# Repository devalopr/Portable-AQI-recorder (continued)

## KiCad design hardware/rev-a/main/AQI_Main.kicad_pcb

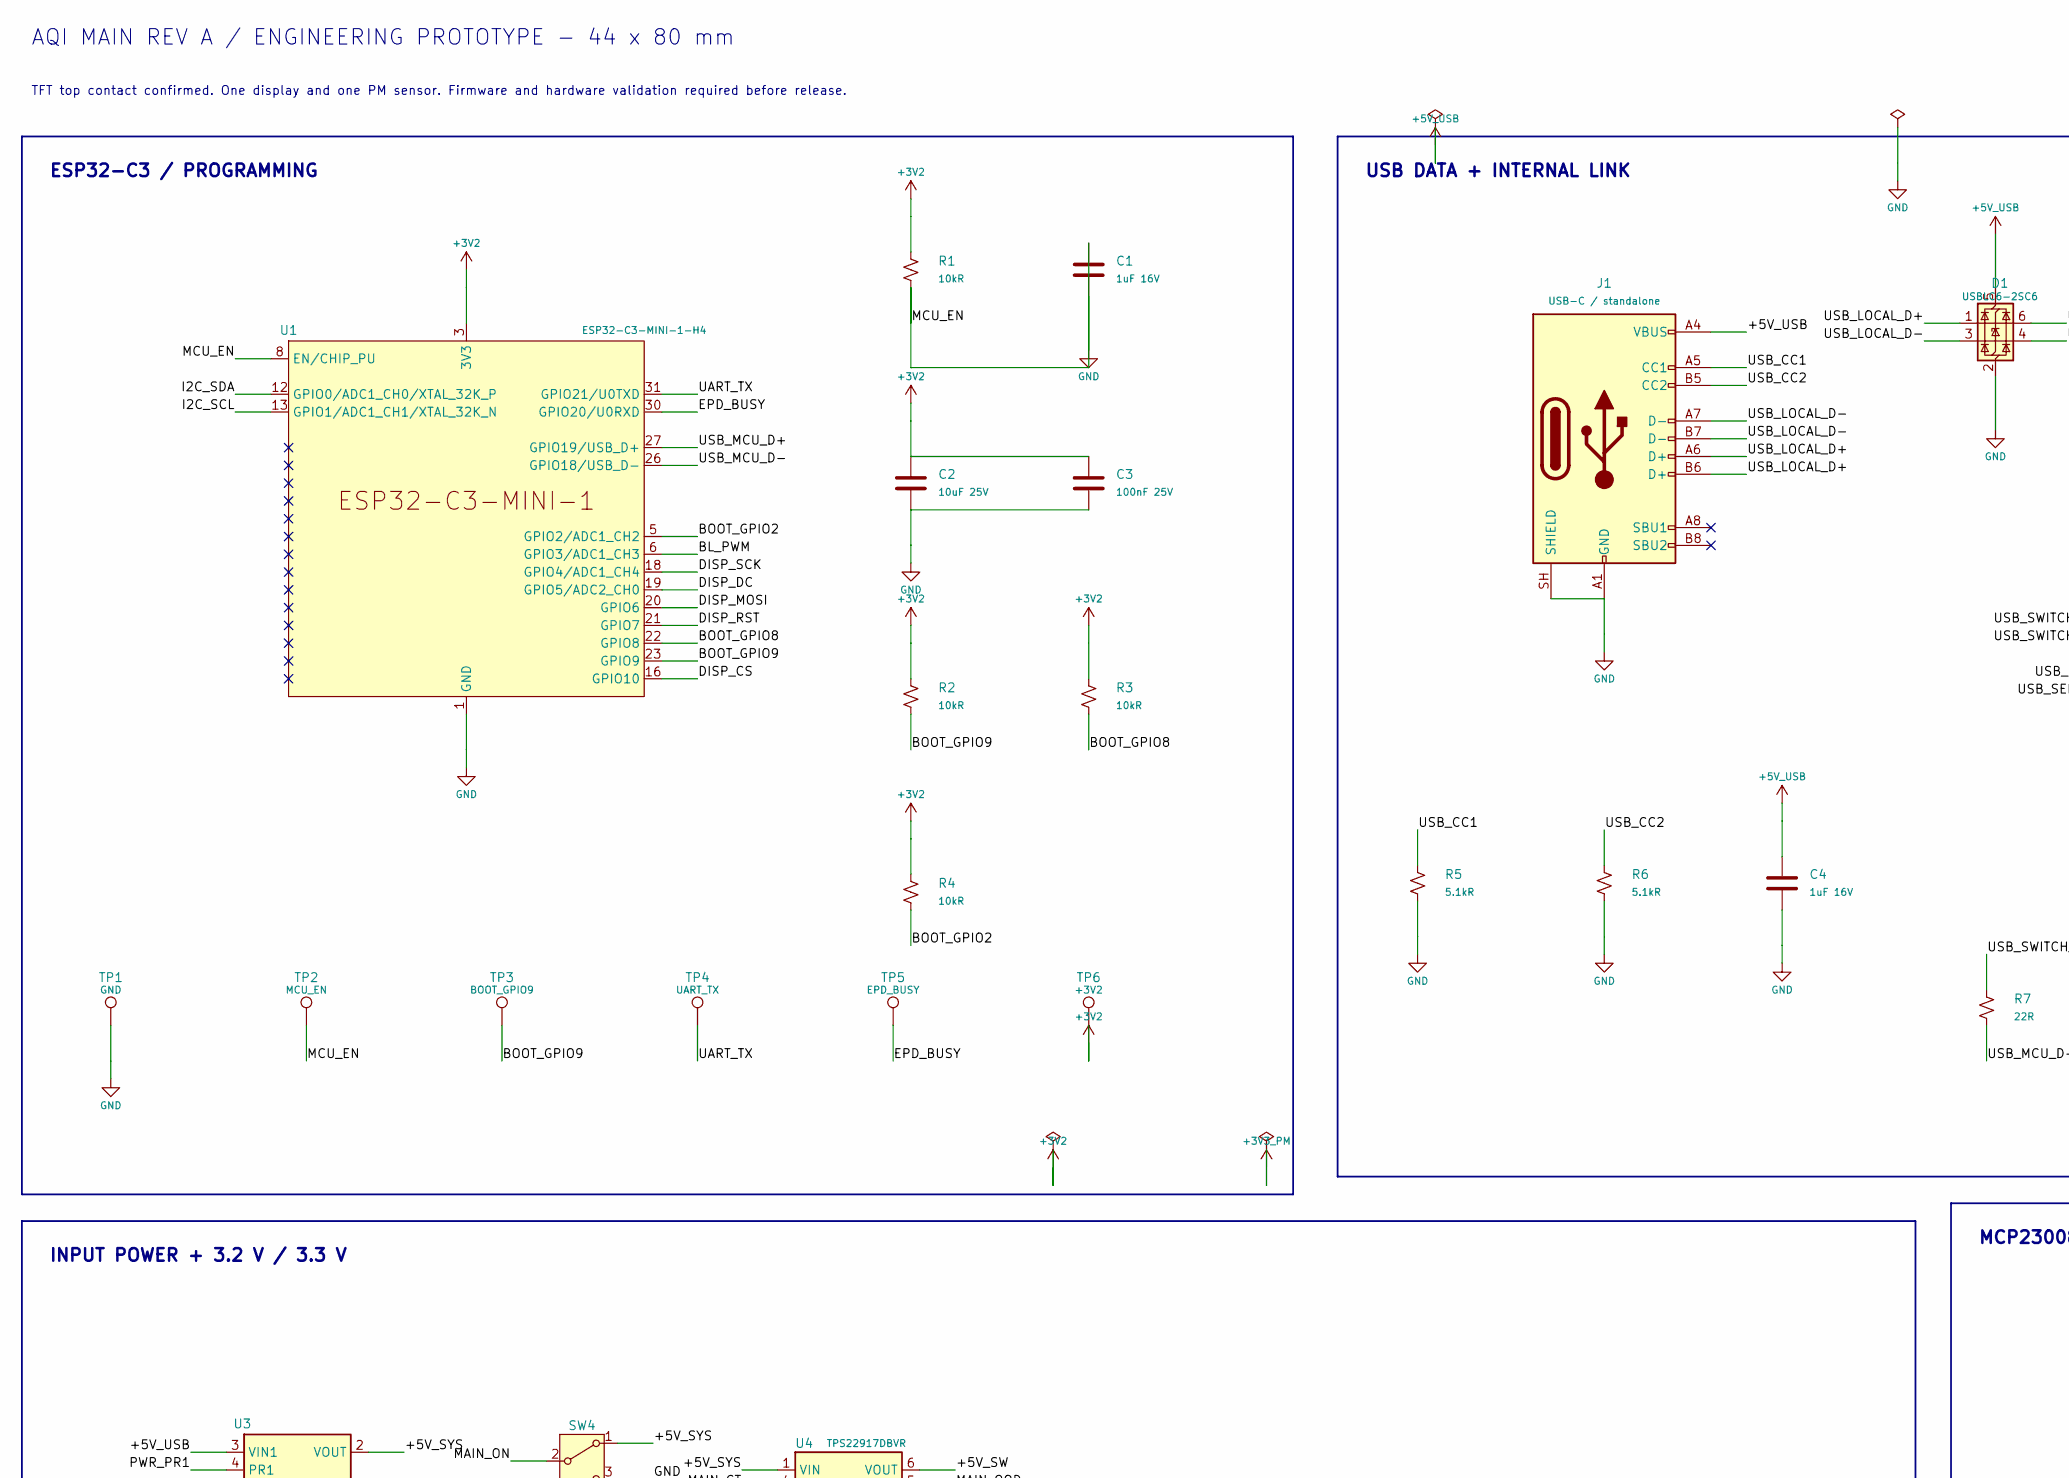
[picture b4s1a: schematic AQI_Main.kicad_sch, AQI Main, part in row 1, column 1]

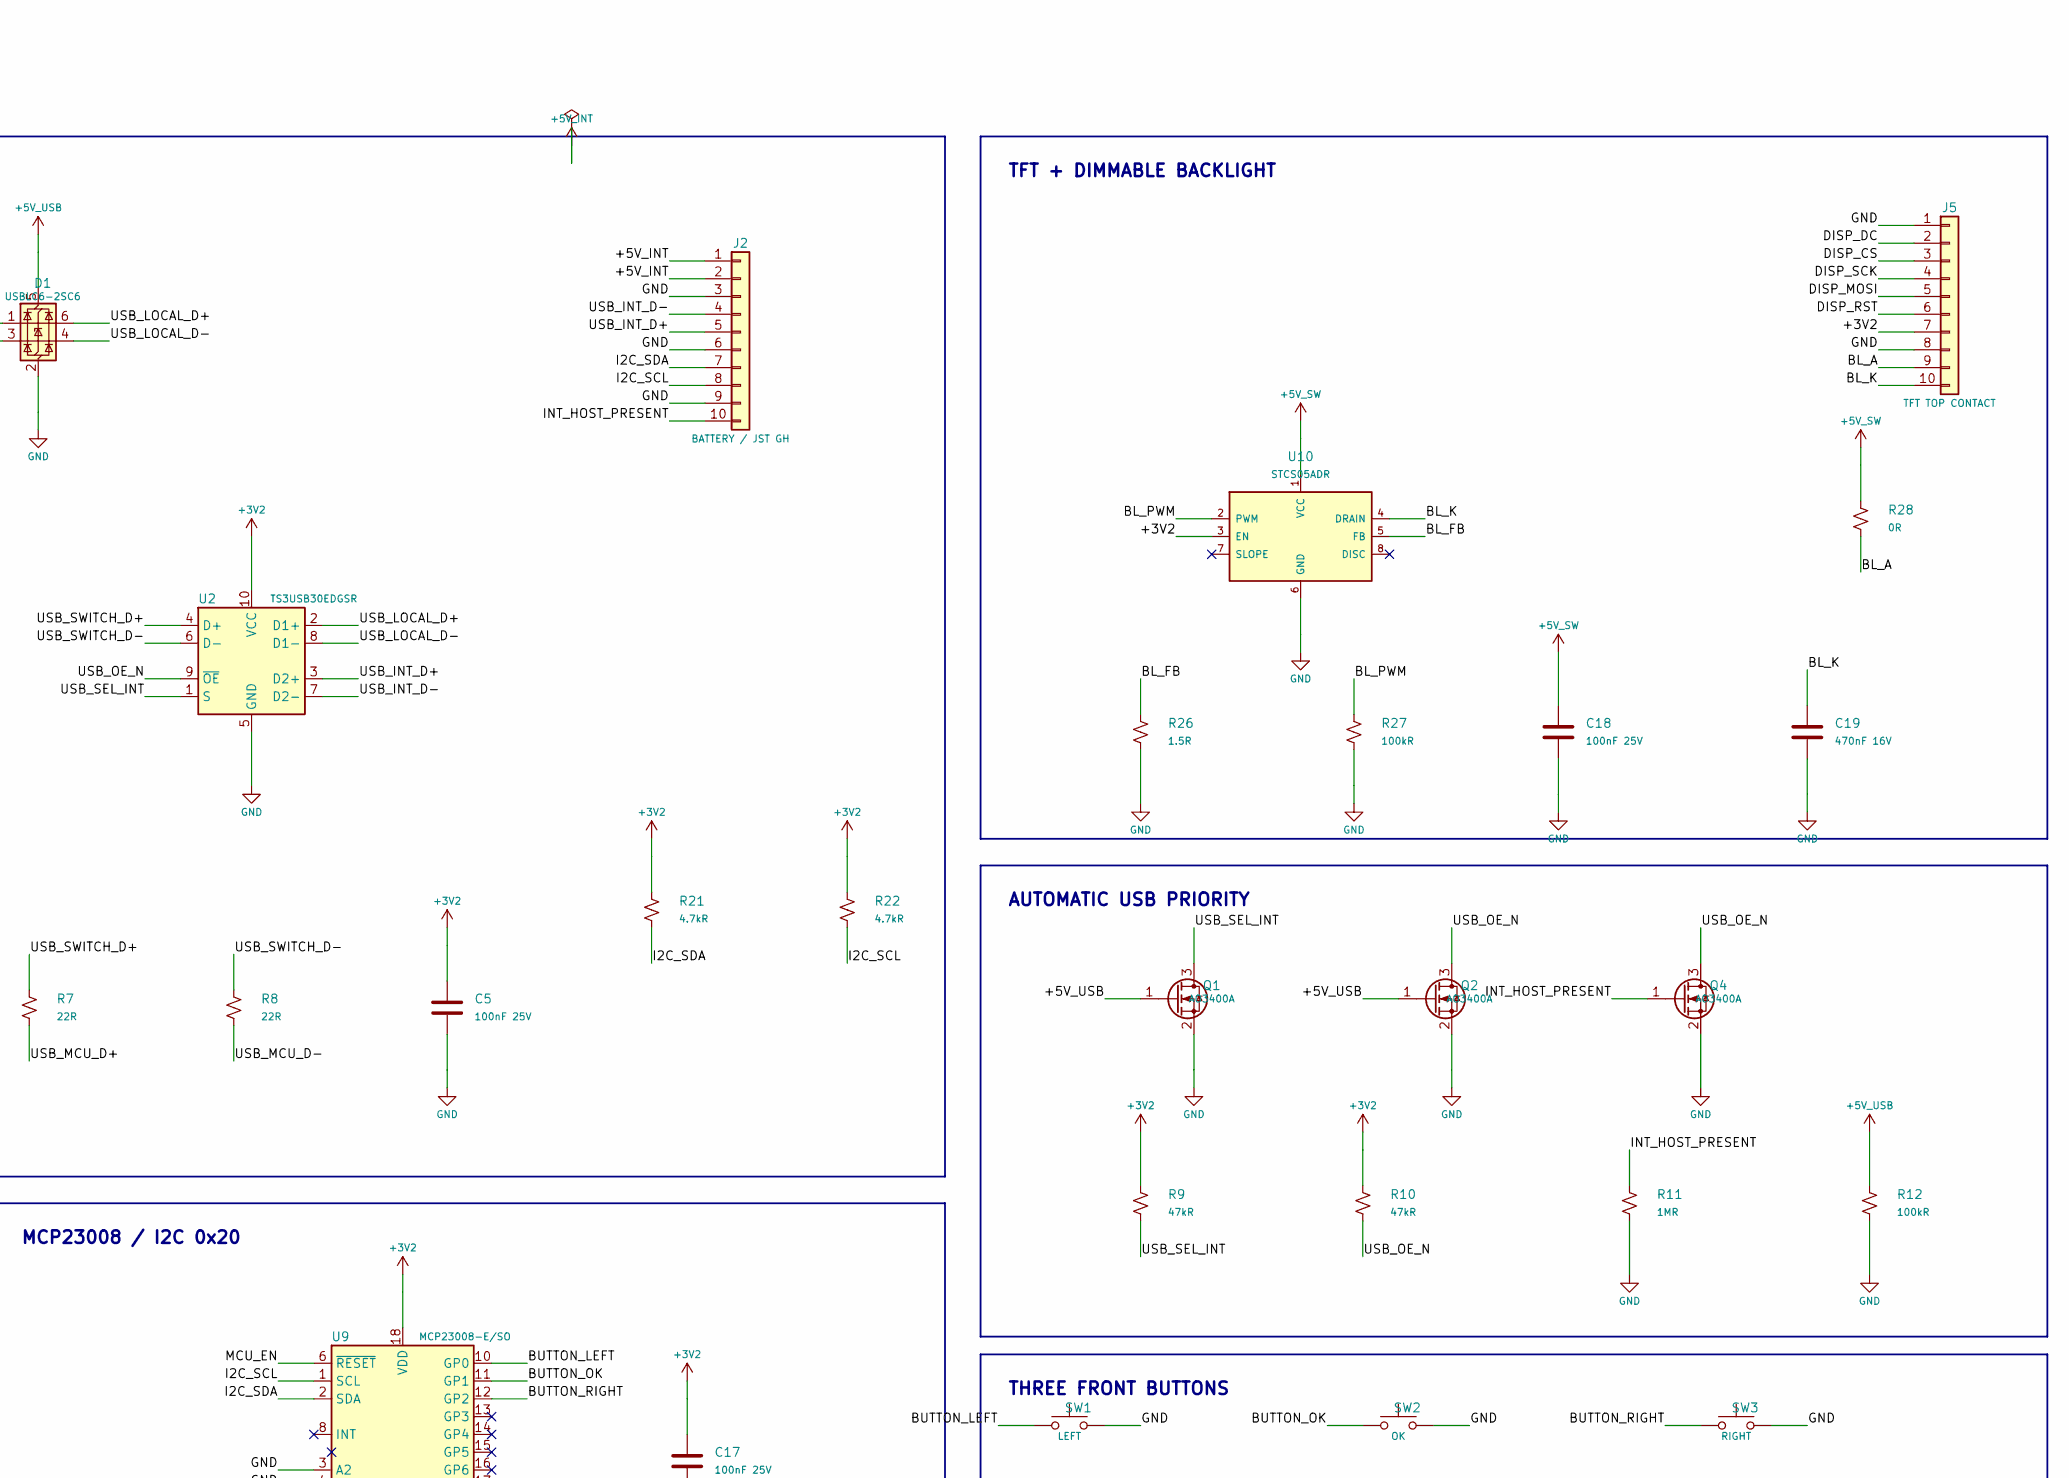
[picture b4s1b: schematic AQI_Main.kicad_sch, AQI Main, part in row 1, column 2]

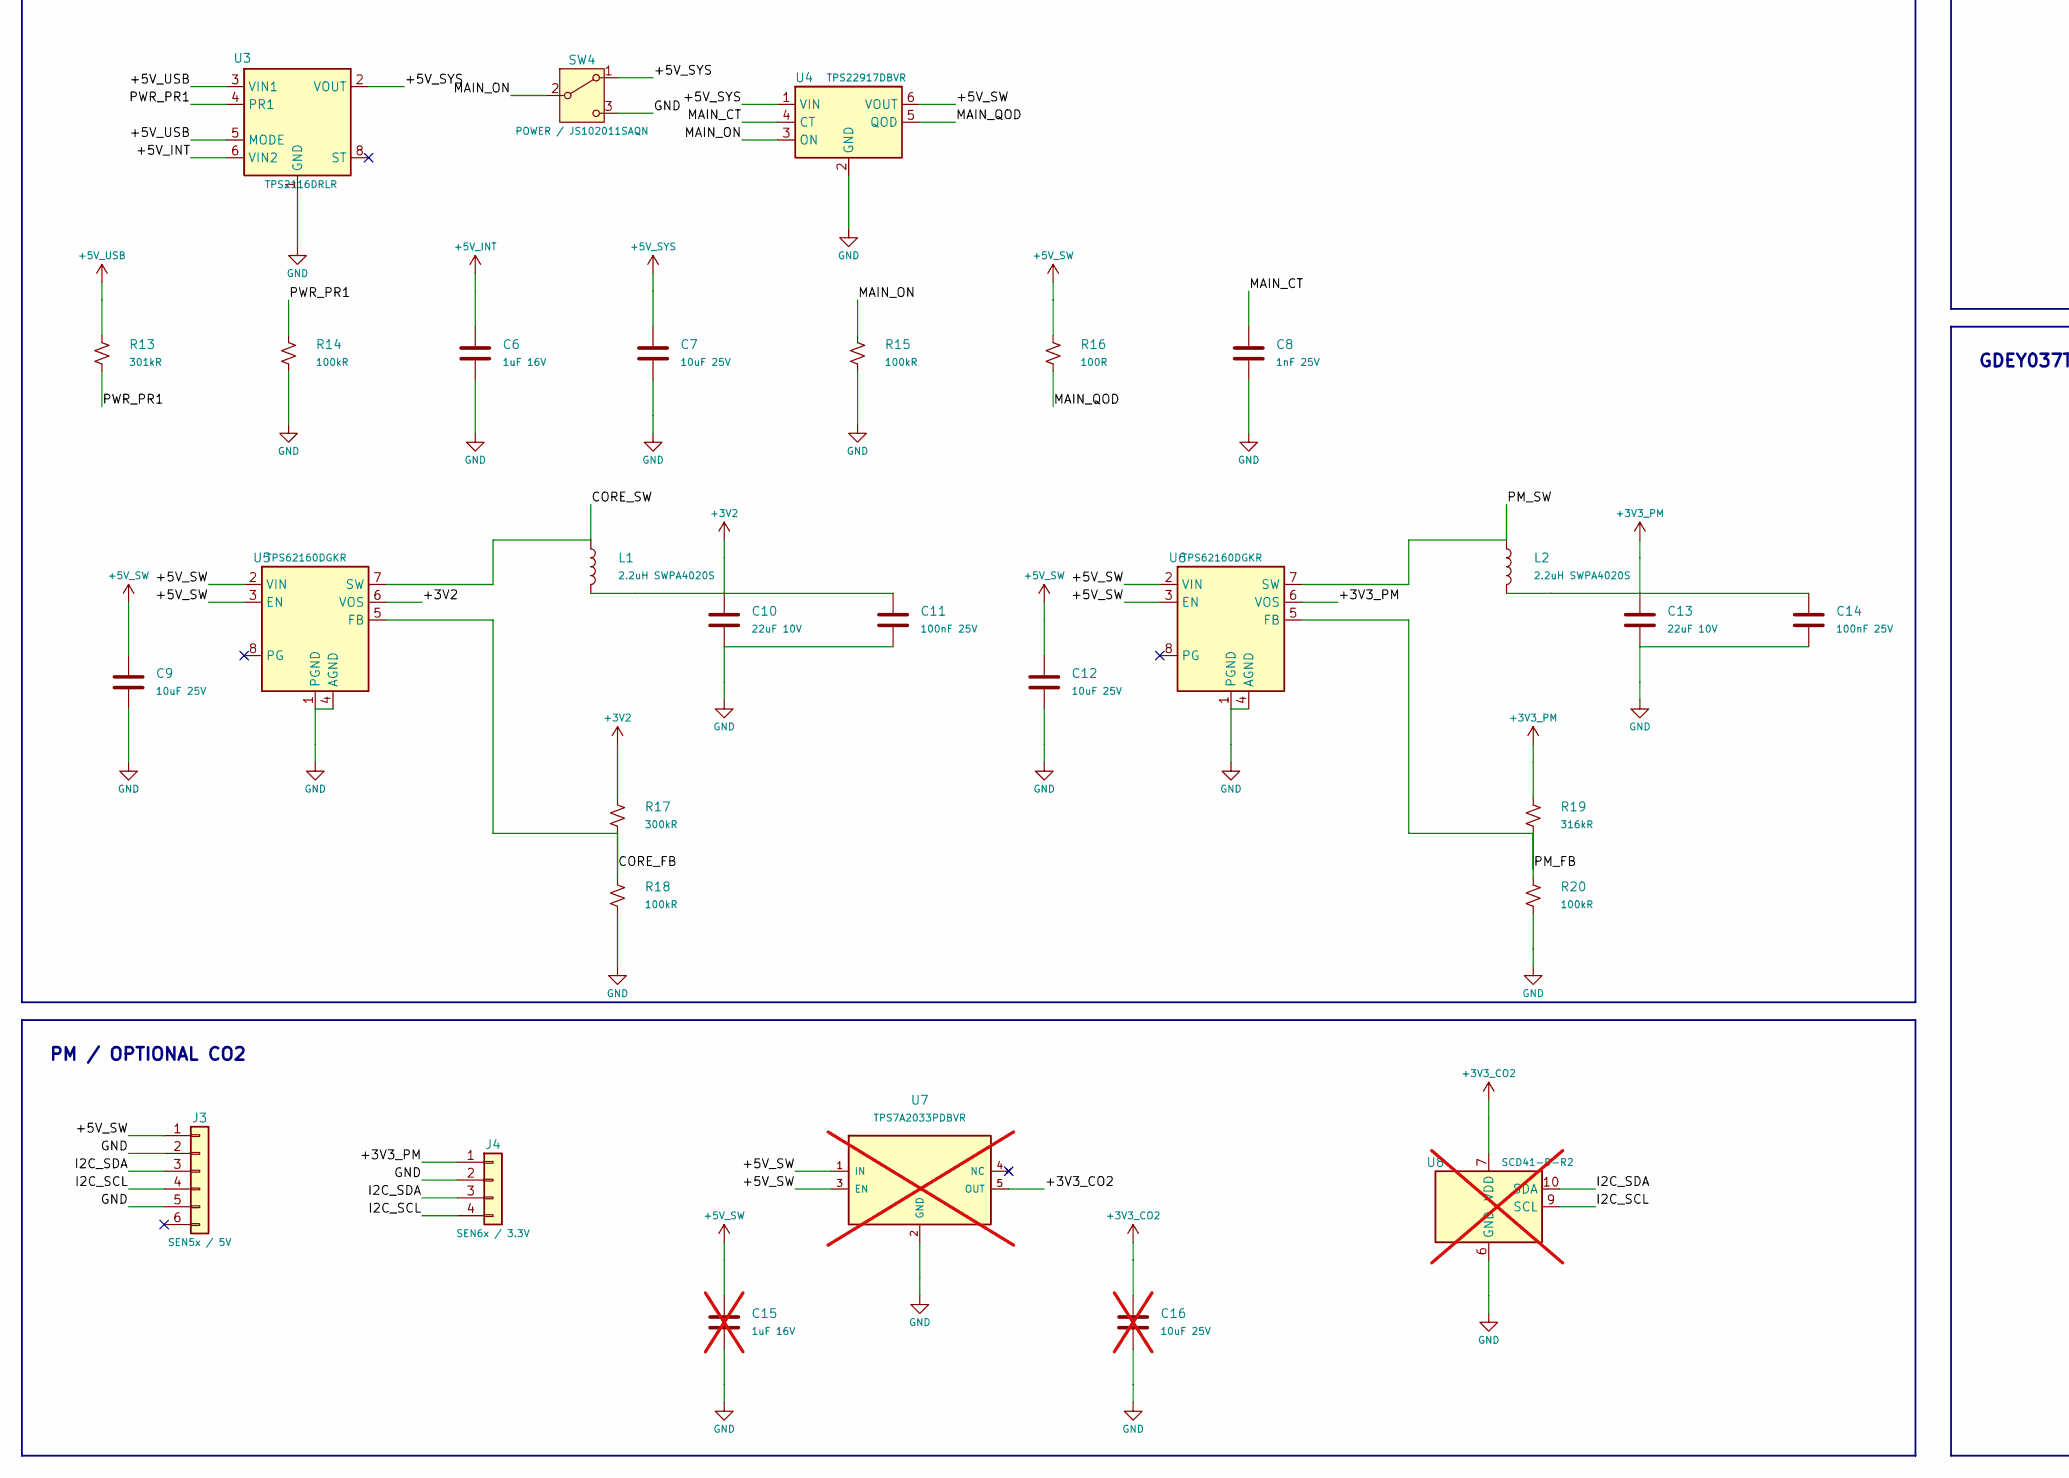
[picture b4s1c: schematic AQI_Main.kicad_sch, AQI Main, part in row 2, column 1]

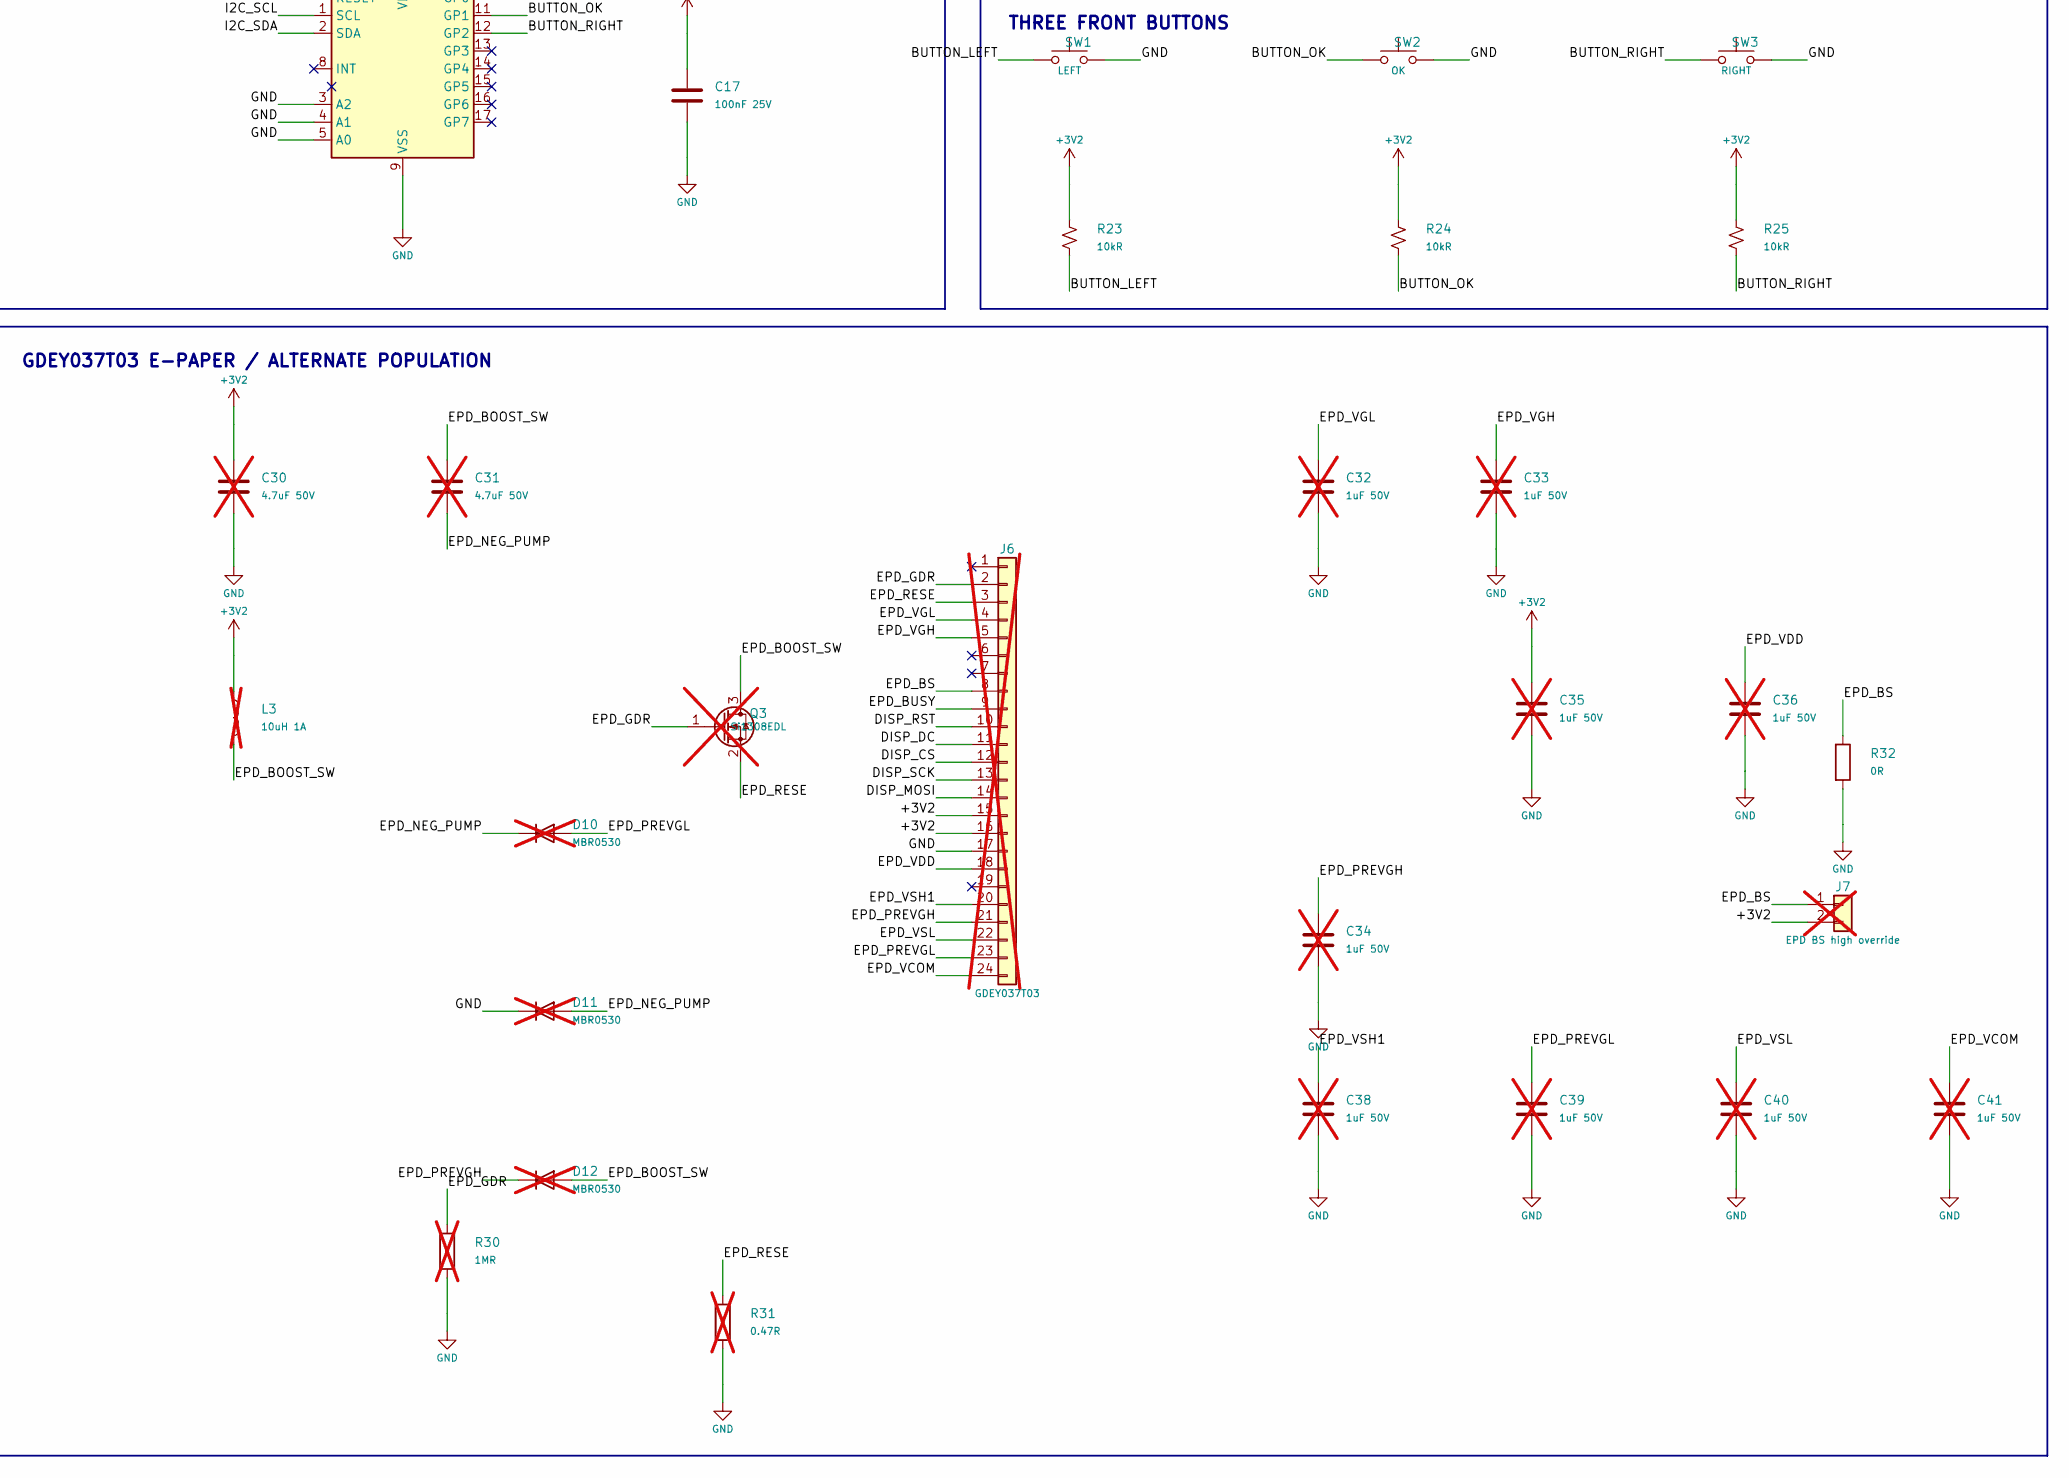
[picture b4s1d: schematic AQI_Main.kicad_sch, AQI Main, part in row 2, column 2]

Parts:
C1, C4, C6: 1uF 16V; C_0603_1608Metric
C2, C7, C9, C12: 10uF 25V; C_0805_2012Metric
C3, C5, C11, C14, C17, C18: 100nF 25V; C_0603_1608Metric
C8: 1nF 25V; C_0603_1608Metric
C10, C13: 22uF 10V; C_0805_2012Metric
C15: 1uF 16V; C_0603_1608Metric; not fitted
C16: 10uF 25V; C_0805_2012Metric; not fitted
C19: 470nF 16V; C_0603_1608Metric
C30, C31: 4.7uF 50V; C_0805_2012Metric; not fitted
C32, C33, C34, C35, C36, C38, C39, C40, C41: 1uF 50V; C_0805_2012Metric; not fitted
D1: USBLC6-2SC6; SOT-23-6; MPN USBLC6-2SC6
D10, D11, D12: MBR0530; D_SOD-123; not fitted
J1: USB-C / standalone; USB_C_Receptacle_GCT_USB4105-xx-A_16P_TopMnt_Horizontal; MPN USB4105-GF-A
J2: BATTERY / JST GH; JST_GH_SM10B-GHS-TB_1x10-1MP_P1.25mm_Horizontal; MPN SM10B-GHS-TB(LF)(SN)
J3: SEN5x / 5V; JST_GH_SM06B-GHS-TB_1x06-1MP_P1.25mm_Horizontal; MPN SM06B-GHS-TB(LF)(SN)
J4: SEN6x / 3.3V; JST_GH_SM04B-GHS-TB_1x04-1MP_P1.25mm_Horizontal; MPN SM04B-GHS-TB(LF)(SN)
J5: TFT TOP CONTACT; TE_1-84953-0_1x10-1MP_P1.0mm_Horizontal; MPN 1-84953-0
J6: GDEY037T03; Hirose_FH12-24S-0.5SH_1x24-1MP_P0.50mm_Horizontal; MPN GDEY037T03; not fitted
J7: EPD BS high override; SolderJumper-2_P1.3mm_Open_Pad1.0x1.5mm; MPN EPD BS high override; not fitted
L1, L2: 2.2uH SWPA4020S; L_Sunlord_SWPA4020S; MPN SWPA4020S2R2MT
L3: 10uH 1A; L_Sunlord_SWPA4020S; MPN SWPA4020S100MT; not fitted
Q1, Q2, Q4: AO3400A; SOT-23; MPN AO3400A
Q3: Si1308EDL; SOT-323_SC-70; MPN Si1308EDL; not fitted
R1, R2, R3, R4, R23, R24, R25: 10kR; R_0603_1608Metric
R5, R6: 5.1kR; R_0603_1608Metric
R7, R8: 22R; R_0603_1608Metric
R9, R10: 47kR; R_0603_1608Metric
R11: 1MR; R_0603_1608Metric
R12, R14, R15, R18, R20, R27: 100kR; R_0603_1608Metric
R13: 301kR; R_0603_1608Metric
R16: 100R; R_0603_1608Metric
R17: 300kR; R_0603_1608Metric
R19: 316kR; R_0603_1608Metric
R21, R22: 4.7kR; R_0603_1608Metric
R26: 1.5R; R_0603_1608Metric
R28, R32: 0R; R_0603_1608Metric
R30: 1MR; R_0603_1608Metric; not fitted
R31: 0.47R; R_0603_1608Metric; not fitted
SW1: LEFT; SW_Push_1P1T_NO_CK_KMR2; MPN KMR221GLFS
SW2: OK; SW_Push_1P1T_NO_CK_KMR2; MPN KMR221GLFS
SW3: RIGHT; SW_Push_1P1T_NO_CK_KMR2; MPN KMR221GLFS
SW4: POWER / JS102011SAQN; SW_SPDT_CK_JS102011SAQN; MPN JS102011SAQN
TP1: GND; TestPoint_Pad_D1.0mm
TP2: MCU_EN; TestPoint_Pad_D1.0mm
TP3: BOOT_GPIO9; TestPoint_Pad_D1.0mm
TP4: UART_TX; TestPoint_Pad_D1.0mm
TP5: EPD_BUSY; TestPoint_Pad_D1.0mm
TP6: +3V2; TestPoint_Pad_D1.0mm
U1: ESP32-C3-MINI-1-H4; ESP32-C3-MINI-1; MPN ESP32-C3-MINI-1-H4
U2: TS3USB30EDGSR; TSSOP-10_3x3mm_P0.5mm; MPN TS3USB30EDGSR
U3: TPS2116DRLR; SOT-583-8; MPN TPS2116DRLR
U4: TPS22917DBVR; SOT-23-6; MPN TPS22917DBVR
U5, U6: TPS62160DGKR; MSOP-8_3x3mm_P0.65mm; MPN TPS62160DGKR
U7: TPS7A2033PDBVR; SOT-23-5; MPN TPS7A2033PDBVR; not fitted
U8: SCD41-D-R2; Sensirion_SCD4x-1EP_10.1x10.1mm_P1.25mm_EP4.8x4.8mm; MPN SCD41-D-R2; not fitted
U9: MCP23008-E/SO; SOIC-18W_7.5x11.6mm_P1.27mm; MPN MCP23008-E/SO
U10: STCS05ADR; SOIC-8_3.9x4.9mm_P1.27mm; MPN STCS05ADR

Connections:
+3V2: C2.1, C3.1, C5.1, C10.1, C11.1, C17.1, C30.1, C35.1, J5.7, J6.15, J6.16, J7.2, L1.2, L3.1, R1.1, R2.1, R3.1, R4.1, R9.1, R10.1, R17.1, R21.1, R22.1, R23.1, R24.1, R25.1, TP6.1, U1.3 (3V3), U2.10 (VCC), U5.6 (VOS), U9.18 (VDD), U10.3 (EN)
+3V3_CO2: C16.1, U7.5 (OUT), U8.7 (VDD), U8.19 (VDD)
+3V3_PM: C13.1, C14.1, J4.1, L2.2, R19.1, U6.6 (VOS)
+5V_INT: C6.1, J2.1, J2.2, U3.6 (VIN2)
+5V_SW: C9.1, C12.1, C15.1, C18.1, J3.1, R16.1, R28.1, U4.6 (VOUT), U5.2 (VIN), U5.3 (EN), U6.2 (VIN), U6.3 (EN), U7.1 (IN), U7.3 (EN), U10.1 (VCC)
+5V_SYS: C7.1, SW4.1 (A), U3.2 (VOUT), U3.7 (VOUT), U4.1 (VIN)
+5V_USB: C4.1, D1.5 (VBUS), J1.A4 (VBUS), J1.A9 (VBUS), J1.B4 (VBUS), J1.B9 (VBUS), Q1.1 (G), Q2.1 (G), R12.1, R13.1, U3.3 (VIN1), U3.5 (MODE)
/BL_A: J5.9, R28.2
/BL_FB: R26.1, U10.5 (FB)
/BL_K: C19.1, J5.10, U10.4 (DRAIN)
/BL_PWM: R27.1, U1.6 (GPIO3/ADC1_CH3), U10.2 (PWM)
/BOOT_GPIO2: R4.2, U1.5 (GPIO2/ADC1_CH2)
/BOOT_GPIO8: R3.2, U1.22 (GPIO8)
/BOOT_GPIO9: R2.2, TP3.1, U1.23 (GPIO9)
/BUTTON_LEFT: R23.2, SW1.1, U9.10 (GP0)
/BUTTON_OK: R24.2, SW2.1, U9.11 (GP1)
/BUTTON_RIGHT: R25.2, SW3.1, U9.12 (GP2)
/CORE_FB: R17.2, R18.1, U5.5 (FB)
/CORE_SW: L1.1, U5.7 (SW)
/DISP_CS: J5.3, J6.12, U1.16 (GPIO10)
/DISP_DC: J5.2, J6.11, U1.19 (GPIO5/ADC2_CH0)
/DISP_MOSI: J5.5, J6.14, U1.20 (GPIO6)
/DISP_RST: J5.6, J6.10, U1.21 (GPIO7)
/DISP_SCK: J5.4, J6.13, U1.18 (GPIO4/ADC1_CH4)
/EPD_BOOST_SW: C31.1, D12.2 (A), L3.2, Q3.3 (D)
/EPD_BS: J6.8, J7.1, R32.1
/EPD_BUSY: J6.9, TP5.1, U1.30 (GPIO20/U0RXD)
/EPD_GDR: J6.2, Q3.1 (G), R30.1
/EPD_NEG_PUMP: C31.2, D10.1 (K), D11.2 (A)
/EPD_PREVGH: C34.1, D12.1 (K), J6.21
/EPD_PREVGL: C39.1, D10.2 (A), J6.23
/EPD_RESE: J6.3, Q3.2 (S), R31.1
/EPD_VCOM: C41.1, J6.24
/EPD_VDD: C36.1, J6.18
/EPD_VGH: C33.1, J6.5
/EPD_VGL: C32.1, J6.4
/EPD_VSH1: C38.1, J6.20
/EPD_VSL: C40.1, J6.22
/I2C_SCL: J2.8, J3.4, J4.4, R22.2, U1.13 (GPIO1/ADC1_CH1/XTAL_32K_N), U8.9 (SCL), U9.1 (SCL)
/I2C_SDA: J2.7, J3.3, J4.3, R21.2, U1.12 (GPIO0/ADC1_CH0/XTAL_32K_P), U8.10 (SDA), U9.2 (SDA)
/INT_HOST_PRESENT: J2.10, Q4.1 (G), R11.1
/MAIN_CT: C8.1, U4.4 (CT)
/MAIN_ON: R15.1, SW4.2 (B), U4.3 (ON)
/MAIN_QOD: R16.2, U4.5 (QOD)
/PM_FB: R19.2, R20.1, U6.5 (FB)
/PM_SW: L2.1, U6.7 (SW)
/PWR_PR1: R13.2, R14.1, U3.4 (PR1)
/UART_TX: TP4.1, U1.31 (GPIO21/U0TXD)
/USB_CC1: J1.A5 (CC1), R5.1
/USB_CC2: J1.B5 (CC2), R6.1
/USB_INT_D+: J2.5, U2.3 (D2+)
/USB_INT_D-: J2.4, U2.7 (D2-)
/USB_LOCAL_D+: D1.1 (I/O1), D1.6 (I/O1), J1.A6 (D+), J1.B6 (D+), U2.2 (D1+)
/USB_LOCAL_D-: D1.3 (I/O2), D1.4 (I/O2), J1.A7 (D-), J1.B7 (D-), U2.8 (D1-)
/USB_MCU_D+: R7.2, U1.27 (GPIO19/USB_D+)
/USB_MCU_D-: R8.2, U1.26 (GPIO18/USB_D-)
/USB_OE_N: Q2.3 (D), Q4.3 (D), R10.2, U2.9 (~OE)
/USB_SEL_INT: Q1.3 (D), R9.2, U2.1 (S)
/USB_SWITCH_D+: R7.1, U2.4 (D+)
/USB_SWITCH_D-: R8.1, U2.6 (D-)

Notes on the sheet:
ESP32-C3 / PROGRAMMING
USB DATA + INTERNAL LINK
TFT + DIMMABLE BACKLIGHT
AUTOMATIC USB PRIORITY
INPUT POWER + 3.2 V / 3.3 V
PM / OPTIONAL CO2
MCP23008 / I2C 0x20
THREE FRONT BUTTONS
GDEY037T03 E-PAPER / ALTERNATE POPULATION
AQI MAIN REV A / ENGINEERING PROTOTYPE - 44 x 80 mm
TFT top contact confirmed. One display and one PM sensor. Firmware and hardware validation required before release.

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
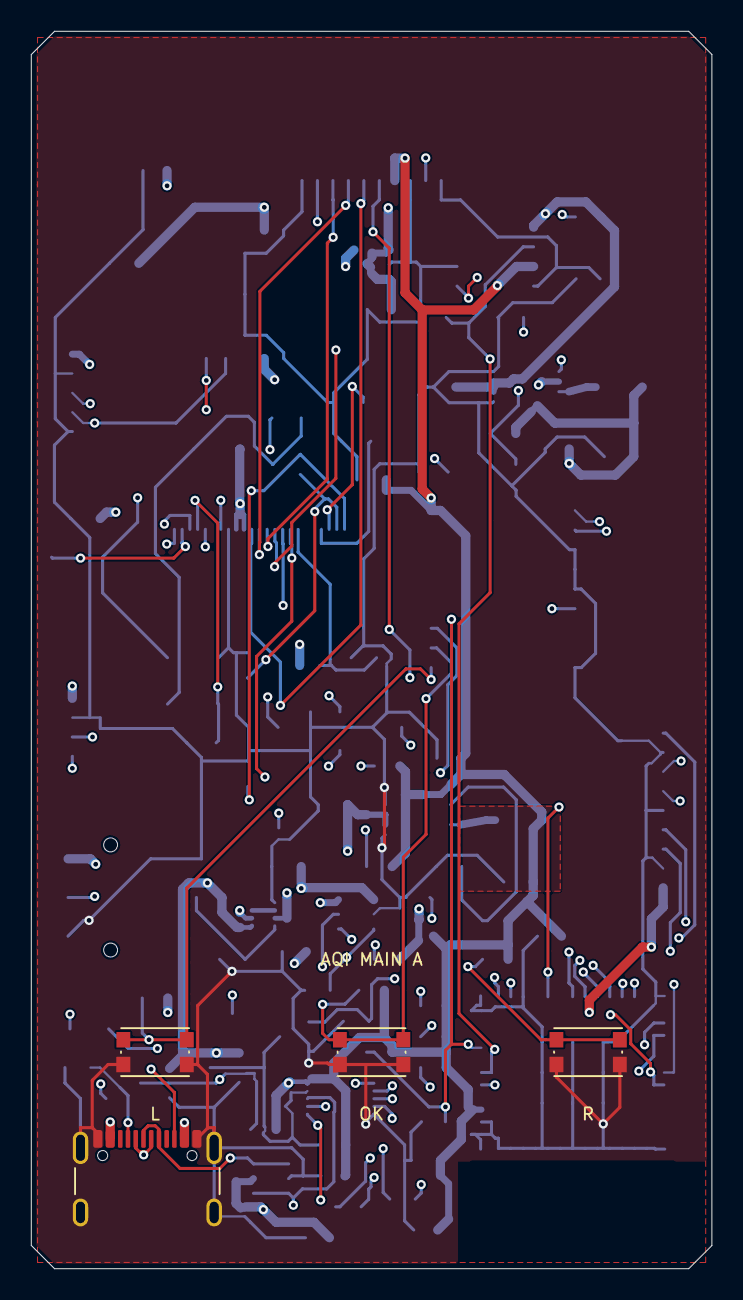
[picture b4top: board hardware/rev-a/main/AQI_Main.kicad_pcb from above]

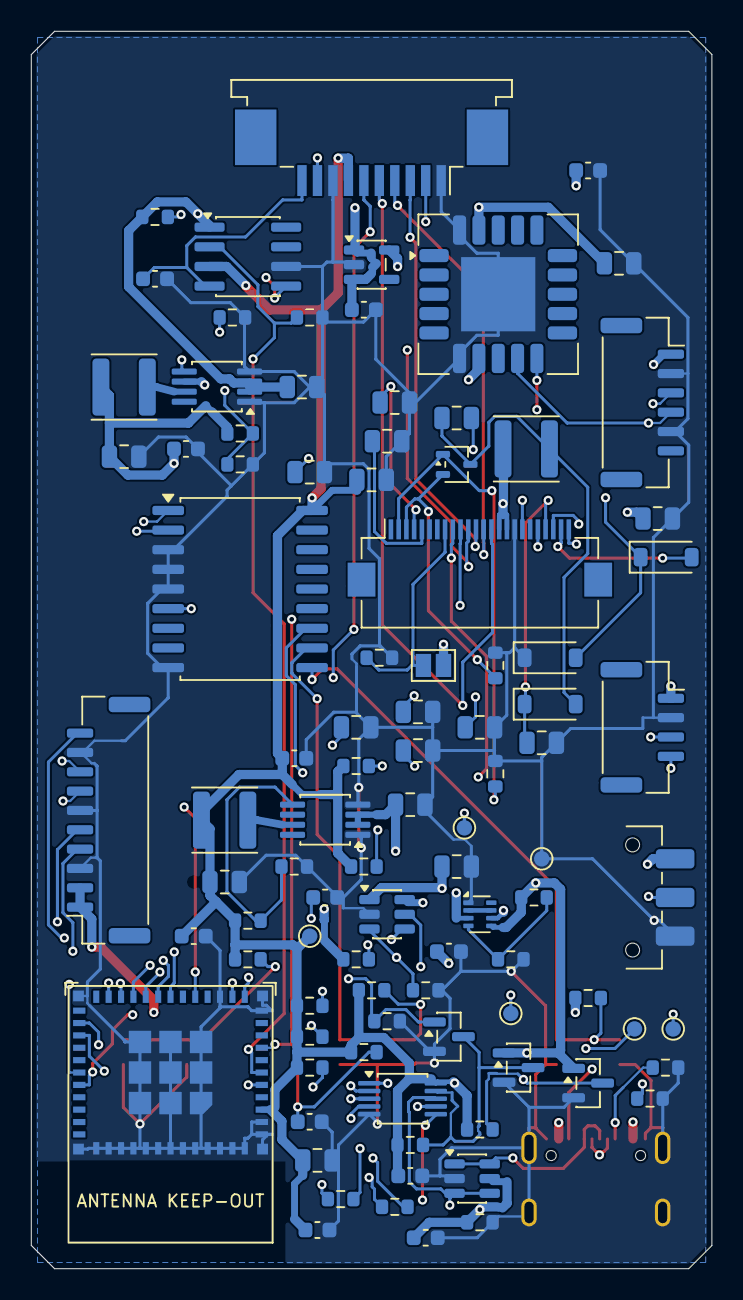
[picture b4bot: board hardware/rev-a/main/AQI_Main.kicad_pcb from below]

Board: 4 copper layers, 44.0 x 80.0 mm, 99 parts (95 on the bottom side), 62 nets.

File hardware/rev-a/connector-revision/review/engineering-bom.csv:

"Reference","Value","MPN","Manufacturer","Footprint","DNP","Datasheet","Assembly note"
"C1","1uF 16V","","","Capacitor_SMD:C_0603_1608Metric","","",""
"C2","10uF 25V","","","Capacitor_SMD:C_0805_2012Metric","","",""
"C3","100nF 25V","","","Capacitor_SMD:C_0603_1608Metric","","",""
"C4","1uF 16V","","","Capacitor_SMD:C_0603_1608Metric","","",""
"C5","100nF 25V","","","Capacitor_SMD:C_0603_1608Metric","","",""
"C6","1uF 16V","","","Capacitor_SMD:C_0603_1608Metric","","",""
"C7","10uF 25V","","","Capacitor_SMD:C_0805_2012Metric","","",""
"C8","1nF 25V","","","Capacitor_SMD:C_0603_1608Metric","","",""
"C9","10uF 25V","","","Capacitor_SMD:C_0805_2012Metric","","",""
"C10","22uF 10V","","","Capacitor_SMD:C_0805_2012Metric","","",""
"C11","100nF 25V","","","Capacitor_SMD:C_0603_1608Metric","","",""
"C12","10uF 25V","","","Capacitor_SMD:C_0805_2012Metric","","",""
"C13","22uF 10V","","","Capacitor_SMD:C_0805_2012Metric","","",""
"C14","100nF 25V","","","Capacitor_SMD:C_0603_1608Metric","","",""
"C15","1uF 16V","","","Capacitor_SMD:C_0603_1608Metric","DNP","",""
"C16","10uF 25V","","","Capacitor_SMD:C_0805_2012Metric","DNP","",""
"C17","100nF 25V","","","Capacitor_SMD:C_0603_1608Metric","","",""
"C18","100nF 25V","","","Capacitor_SMD:C_0603_1608Metric","","",""
"C19","470nF 16V","","","Capacitor_SMD:C_0603_1608Metric","","",""
"C30","4.7uF 50V","","","Capacitor_SMD:C_0805_2012Metric","DNP","",""
"C31","4.7uF 50V","","","Capacitor_SMD:C_0805_2012Metric","DNP","",""
"C32","1uF 50V","","","Capacitor_SMD:C_0805_2012Metric","DNP","",""
"C33","1uF 50V","","","Capacitor_SMD:C_0805_2012Metric","DNP","",""
"C34","1uF 50V","","","Capacitor_SMD:C_0805_2012Metric","DNP","",""
"C35","1uF 50V","","","Capacitor_SMD:C_0805_2012Metric","DNP","",""
"C36","1uF 50V","","","Capacitor_SMD:C_0805_2012Metric","DNP","",""
"C38","1uF 50V","","","Capacitor_SMD:C_0805_2012Metric","DNP","",""
"C39","1uF 50V","","","Capacitor_SMD:C_0805_2012Metric","DNP","",""
"C40","1uF 50V","","","Capacitor_SMD:C_0805_2012Metric","DNP","",""
"C41","1uF 50V","","","Capacitor_SMD:C_0805_2012Metric","DNP","",""
"C42","100nF 16V","","","Capacitor_SMD:C_0402_1005Metric","DNP","",""
"D1","USBLC6-2SC6","USBLC6-2SC6","STMicroelectronics","Package_TO_SOT_SMD:SOT-23-6","","",""
"D10","MBR0530","","","Diode_SMD:D_SOD-123","DNP","",""
"D11","MBR0530","","","Diode_SMD:D_SOD-123","DNP","",""
"D12","MBR0530","","","Diode_SMD:D_SOD-123","DNP","",""
"J1","USB-C / standalone","USB4105-GF-A","GCT","Connector_USB:USB_C_Receptacle_GCT_USB4105-xx-A_16P_TopMnt_Horizontal","","",""
"J2","BATTERY / JST GH","SM10B-GHS-TB(LF)(SN)","JST","Connector_JST:JST_GH_SM10B-GHS-TB_1x10-1MP_P1.25mm_Horizontal","","",""
"J3","SEN5x / 5V","SM06B-GHS-TB(LF)(SN)","JST","Connector_JST:JST_GH_SM06B-GHS-TB_1x06-1MP_P1.25mm_Horizontal","","",""
"J4","SEN6x / 3.3V","SM04B-GHS-TB(LF)(SN)","JST","Connector_JST:JST_GH_SM04B-GHS-TB_1x04-1MP_P1.25mm_Horizontal","","","Custom 4-to-6 cable. Sensor pins5/6 open; pin1 3.3V,2GND,3SDA,4SCL."
"J5","TFT TOP CONTACT","1-84953-0","TE Connectivity","Connector_FFC-FPC:TE_1-84953-0_1x10-1MP_P1.0mm_Horizontal","","",""
"J6","GDEY037T03","GDEY037T03","","Connector_FFC-FPC:Hirose_FH12-24S-0.5SH_1x24-1MP_P0.50mm_Horizontal","DNP","",""
"J7","EPD BS high override","EPD BS high override","","Jumper:SolderJumper-2_P1.3mm_Open_Pad1.0x1.5mm","DNP","","Remove R32 before bridging J7. Default BS low matches vendor circuit."
"L1","2.2uH SWPA4020S","SWPA4020S2R2MT","Sunlord","Inductor_SMD:L_Sunlord_SWPA4020S","","",""
"L2","2.2uH SWPA4020S","SWPA4020S2R2MT","Sunlord","Inductor_SMD:L_Sunlord_SWPA4020S","","",""
"L3","10uH 1A","SWPA4020S100MT","","Inductor_SMD:L_Sunlord_SWPA4020S","DNP","",""
"Q1","AO3400A","AO3400A","Alpha & Omega Semiconductor","Package_TO_SOT_SMD:SOT-23","","https://www.aosmd.com/sites/default/files/res/data_sheets/AO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",""
"Q2","AO3400A","AO3400A","Alpha & Omega Semiconductor","Package_TO_SOT_SMD:SOT-23","","https://www.aosmd.com/sites/default/files/res/data_sheets/AO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",""
"Q3","Si1308EDL","Si1308EDL","","Package_TO_SOT_SMD:SOT-323_SC-70","DNP","",""
"Q4","AO3400A","AO3400A","Alpha & Omega Semiconductor","Package_TO_SOT_SMD:SOT-23","","https://www.aosmd.com/sites/default/files/res/data_sheets/AO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",""
"R1","10kR","","","Resistor_SMD:R_0603_1608Metric","","",""
"R2","10kR","","","Resistor_SMD:R_0603_1608Metric","","",""
"R3","10kR","","","Resistor_SMD:R_0603_1608Metric","","",""
"R4","10kR","","","Resistor_SMD:R_0603_1608Metric","","",""
"R5","5.1kR","","","Resistor_SMD:R_0603_1608Metric","","",""
"R6","5.1kR","","","Resistor_SMD:R_0603_1608Metric","","",""
"R7","22R","","","Resistor_SMD:R_0603_1608Metric","","",""
"R8","22R","","","Resistor_SMD:R_0603_1608Metric","","",""
"R9","47kR","","","Resistor_SMD:R_0603_1608Metric","","",""
"R10","47kR","","","Resistor_SMD:R_0603_1608Metric","","",""
"R11","1MR","","","Resistor_SMD:R_0603_1608Metric","","",""
"R12","100kR","","","Resistor_SMD:R_0603_1608Metric","","",""
"R13","301kR","","","Resistor_SMD:R_0603_1608Metric","","",""
"R14","100kR","","","Resistor_SMD:R_0603_1608Metric","","",""
"R15","100kR","","","Resistor_SMD:R_0603_1608Metric","","",""
"R16","100R","","","Resistor_SMD:R_0603_1608Metric","","",""
"R17","300kR","","","Resistor_SMD:R_0603_1608Metric","","",""
"R18","100kR","","","Resistor_SMD:R_0603_1608Metric","","",""
"R19","316kR","","","Resistor_SMD:R_0603_1608Metric","","",""
"R20","100kR","","","Resistor_SMD:R_0603_1608Metric","","",""
"R21","4.7kR","","","Resistor_SMD:R_0603_1608Metric","","",""
"R22","4.7kR","","","Resistor_SMD:R_0603_1608Metric","","",""
"R23","10kR","","","Resistor_SMD:R_0603_1608Metric","","",""
"R24","10kR","","","Resistor_SMD:R_0603_1608Metric","","",""
"R25","10kR","","","Resistor_SMD:R_0603_1608Metric","","",""
"R26","1.5R","","","Resistor_SMD:R_0603_1608Metric","","",""
"R27","100kR","","","Resistor_SMD:R_0603_1608Metric","","",""
"R28","0R","","","Resistor_SMD:R_0603_1608Metric","","",""
"R30","1MR","","","Resistor_SMD:R_0603_1608Metric","DNP","",""
"R31","0.47R","","","Resistor_SMD:R_0603_1608Metric","DNP","",""
"R32","0R","","","Resistor_SMD:R_0603_1608Metric","","",""
"SW1","LEFT","KMR221GLFS","C&K","Button_Switch_SMD:SW_Push_1P1T_NO_CK_KMR2","","",""
"SW2","OK","KMR221GLFS","C&K","Button_Switch_SMD:SW_Push_1P1T_NO_CK_KMR2","","",""
"SW3","RIGHT","KMR221GLFS","C&K","Button_Switch_SMD:SW_Push_1P1T_NO_CK_KMR2","","",""
"SW4","POWER / JS102011SAQN","JS102011SAQN","C&K","Button_Switch_SMD:SW_SPDT_CK_JS102011SAQN","","",""
"TP1","GND","","","TestPoint:TestPoint_Pad_D1.0mm","","",""
"TP2","MCU_EN","","","TestPoint:TestPoint_Pad_D1.0mm","","",""
"TP3","BOOT_GPIO9","","","TestPoint:TestPoint_Pad_D1.0mm","","",""
"TP4","UART_TX","","","TestPoint:TestPoint_Pad_D1.0mm","","",""
"TP5","EPD_BUSY","","","TestPoint:TestPoint_Pad_D1.0mm","","",""
"TP6","+3V2","","","TestPoint:TestPoint_Pad_D1.0mm","","",""
"U1","ESP32-C3-MINI-1-H4","ESP32-C3-MINI-1-H4","Espressif","AQI:ESP32-C3-MINI-1","","https://documentation.espressif.com/esp32-c3-mini-1_datashee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",""
"U2","TS3USB30EDGSR","TS3USB30EDGSR","Texas Instruments","Package_SO:TSSOP-10_3x3mm_P0.5mm","","",""
"U3","TPS2116DRLR","TPS2116DRLR","Texas Instruments","Package_TO_SOT_SMD:SOT-583-8","","",""
"U4","TPS22917DBVR","TPS22917DBVR","Texas Instruments","Package_TO_SOT_SMD:SOT-23-6","","",""
"U5","TPS62160DGKR","TPS62160DGKR","Texas Instruments","Package_SO:MSOP-8_3x3mm_P0.65mm","","",""
"U6","TPS62160DGKR","TPS62160DGKR","Texas Instruments","Package_SO:MSOP-8_3x3mm_P0.65mm","","",""
"U7","TPS7A2033PDBVR","TPS7A2033PDBVR","Texas Instruments","Package_TO_SOT_SMD:SOT-23-5","DNP","",""
"U8","SCD41-D-R2","SCD41-D-R2","Sensirion","Sensor:Sensirion_SCD4x-1EP_10.1x10.1mm_P1.25mm_EP4.8x4.8mm","DNP","","Optional; vented sensor body 10.1x10.1mm, clearance and thermal review required"
"U9","MCP23008-E/SO","MCP23008-E/SO","Microchip","Package_SO:SOIC-18W_7.5x11.6mm_P1.27mm","","",""
"U10","STCS05ADR","STCS05ADR","STMicroelectronics","Package_SO:SOIC-8_3.9x4.9mm_P1.27mm","","",""

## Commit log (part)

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2026-03-04 Working code; Fixed libraries
2026-03-10 Added support for SEN54 and SEN55
2026-04-13 V2 changes
2026-04-24 Added display and buttons
2026-04-26 Gemini's UI
2026-04-26 CodeX UI- light mode
2026-04-26 Web app done
2026-04-26 BLE connectivity fixed
2026-05-03 Figma UI by codex
2026-05-03 Gemini fixed UI spillage
2026-05-03 UI fixes
2026-05-03 Cleaned up stuff
